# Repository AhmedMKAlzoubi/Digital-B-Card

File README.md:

# Digital Business Card (Digital-B-Card)

An ESP32-C3 based digital business card / badge with an e-paper display and NFC tap-to-share, designed as a custom PCB in a compact card/badge form factor.

## Overview

This project is a self-contained electronic business card. It combines a low-power microcontroller, an e-paper display for a persistent, battery-friendly visual, and an NFC tag for one-tap contact sharing on any NFC-enabled phone. The board is designed to fit inside a 3D-printed badge enclosure.

## Key Features

- **MCU:** ESP32-C3-MINI-1-N4 (RISC-V, Wi-Fi / BLE, native USB) for control logic and OTA wireless updates.
- **Display:** 2.66" e-paper panel (GDEM0266T71WT) driven by the SSD1680 controller — ultra-low power, always-on readability.
- **NFC:** NXP NT3H2111 NTAG I²C tag + custom 8-turn PCB antenna for tap-to-share contact info with any NFC-enabled phone.
- **Power:** MCP73871-2CC power-path LiPo charger + MAX17048 fuel gauge + AP2112K-3.3 LDO — USB-C charging with seamless battery monitoring.
- **Custom PCB:** Designed in KiCad, fabricated as a 2-layer, single-sided 100 × 60 mm board.
- **Custom Case:** 3D-modeled badge enclosure (FreeCAD) with an optional 3D nameplate.

## Repository Structure

| Folder / File | Description |
|---|---|
| `PCB-Schem/` | KiCad schematic (`.kicad_sch`) and PCB layout (`.kicad_pcb`) source files. |
| `Gerber/` | Fabrication-ready Gerber files, drill files, job file, and `gerber.7z` for direct upload to a PCB manufacturer. |
| `BOM/` | Bill of materials (`digital card-BOM.csv`). |
| `datasheets/` | Component datasheets and reference documents (see [Datasheets & Spec Sheets](#datasheets--spec-sheets) below). |
| `Case/` | FreeCAD badge case models (`Digital_Card_Case_3_BADGE.FCStd`), a backup revision, and a 3D nameplate (`case-nameplate.glb`). |
| `Digital_C-Case_Viewer.html` | Standalone browser-based 3D viewer for the case / nameplate model. |
| `DOC/` | Full project report (`Digital_Business_Card_Report.zip`) covering design decisions, testing, and build notes. |

---

## Specification Sheet

> Rev A — 2026-08-24. Values are marked **[V]** verified against a datasheet/layout/CAD, **[E]** estimated, or **[TBC]** to be confirmed on hardware.

### At a Glance

| Parameter | Value |
|---|---|
| Function | E-paper display with NFC tap-to-share and Wi-Fi / BLE connectivity |
| Modes | Desk nameplate / event badge / tap-to-share card (firmware-selected) |
| Outer dimensions | 104.6 × 69.6 × 11.1 mm **[V]** |
| Mass, assembled | ≈ 68 g **[E]** |
| Power | 1S Li-Po, USB-C rechargeable |
| Enclosure | Two-part 3D print, M2 screws |
| MCU | ESP32-C3-MINI-1-N4 (RISC-V, Wi-Fi + BLE, native USB) |
| Display | 2.66" e-paper, 152 × 296 px, SSD1680 driver (GDEM0266T71WT) |
| Connectivity | NFC (NT3H2111 + custom PCB antenna), Wi-Fi, BLE |
| Charging | USB-C, MCP73871-2CC power-path Li-Po charge management |
| Regulation | AP2112K-3.3 LDO |
| Fuel gauge | MAX17048 |
| Battery | 1S Li-Po, 500 mAh (Uxney 503035, 200–600 mAh range supported) |
| Design tool | KiCad |
| Manufacturing | JLCPCB, 2-layer, full SMT assembly |

### PCB Mechanical

| Parameter | Value |
|---|---|
| Outline | 100.0 × 60.0 mm **[V]** |
| Thickness | 1.6 mm **[V]** |
| Layers | 2 (F.Cu, B.Cu) **[V]** |
| Assembly | Single-sided — all components on B.Cu **[V]** |
| Mounting holes | 4 × Ø2.2 mm NPTH for M2, 2.75 mm from each corner **[V]** |
| Min track width | 0.25 mm signal / 0.40 mm power **[V]** |
| Min clearance | 0.20 mm (0.50 mm on HV class) **[V]** |
| Via / drill | 0.6 / 0.3 mm **[V]** |
| Surface finish | ENIG recommended |
| Placements | 59 across 27 orderable line items **[V]** |

### Enclosure

| Parameter | Value |
|---|---|
| Outer | 104.6 × 69.6 × 11.1 mm **[V]** |
| Wall / floor thickness | 2.0 mm **[V]** |
| PCB fit clearance | 0.3 mm per side **[V]** (may open to 0.4–0.5 mm **[TBC]**) |
| Split line | z = +1.6 mm — tray below, cover above **[V]** |
| Internal cavity | 100.6 × 65.6 × 5.5 mm deep **[V]** |
| Board support | 4 × Ø4.5 mm bosses with Ø1.7 mm pilot holes **[V]** |
| Fasteners | 4 × M2 self-tapping; nylon in the two holes nearest the NFC coil |
| USB-C opening | 12.6 × 6.2 mm **[V]** |
| Button access | 2 × Ø2.0 mm through tray floor **[V]** |

### Display

| Parameter | Value |
|---|---|
| Part | GDEM0266T71WT (Good Display) |
| Technology | E-paper, monochrome, bistable — zero power to hold image |
| Controller | SSD1680 (Solomon Systech) |
| Diagonal | 2.66" |
| Resolution | 152 × 296 px **[V]** |
| Active area | 30.704 × 60.088 mm **[V]** |
| Interface | 4-wire SPI, BS1 strapped low **[V]** |
| Connector | 24-pin 0.5 mm FPC, 14 mm tail **[V]** |
| Typical operating current | 4.5 mA **[V]** |
| Peak refresh current | 40 mA typ / 60 mA max **[V]** |

### Wireless

| Parameter | Value |
|---|---|
| MCU module | ESP32-C3-MINI-1-N4 (Espressif), RF pre-certified |
| Core | 32-bit RISC-V single core |
| Flash | 4 MB |
| Wi-Fi | 802.11 b/g/n, 2.4 GHz |
| Bluetooth | BLE 5 |
| Wi-Fi/BLE Antenna | Integrated module PCB antenna, overhanging board edge per Espressif guidance **[V]** |
| USB | Native USB (GPIO18/19) — programming and debug, no UART bridge |

### NFC

| Parameter | Value |
|---|---|
| Tag IC | NT3H2111W0FHKH (NXP NTAG I²C plus) |
| Standard | NFC Forum Type 2, 13.56 MHz |
| Host interface | I²C |
| Antenna | Custom PCB coil on F.Cu — 8 turns, 0.6 mm trace, 0.3 mm gap **[V]** |
| Coil area | 15 × 50 mm **[V]** |
| Coil inductance | ≈ 1.93 µH **[E]** |
| Chip capacitance | 50 pF **[V]** (datasheet §13.1) |
| Tuning capacitor | 22 pF C0G/NP0 **[V]** |
| Field-detect | FD → GPIO3, deep-sleep wake on tap **[V]** |
| Read range | **[TBC]** — C14 is the tuning point |

### Power

| Parameter | Value |
|---|---|
| Battery chemistry | Lithium polymer, 1 cell |
| Capacity | 500 mAh (200–600 mAh range supported) |
| Nominal / max voltage | 3.7 V / 4.2 V |
| Cell | Uxney 503035, 35 × 30 × 5 mm, integrated protection |
| Connector | JST-PH 2.0 mm, S2B-PH-SM4-TB horizontal SMT **[V]** |
| Regulation output | 3.3 V (AP2112K LDO, 600 mA rated) |
| LDO input source | Charger SYS/OUT rail — **not** VBAT |
| Charge IC | MCP73871-2CC, power-path topology |
| Charge voltage | 4.20 V **[V]** |
| Input current limit | 500 mA **[V]** |
| Charge current | ≈ 303 mA **[E]** |
| Termination current | ≈ 42 mA **[E]** |
| Safety timer | 6 h **[V]** |
| Worst-case dissipation | ≈ 0.4 W **[E]** |
| Fuel gauge | MAX17048, ModelGauge, 3 µA operating, I²C, ALRT → GPIO4 wake |

### Current Budget

| State | Estimate | Note |
|---|---|---|
| Deep sleep | ≈ 10–20 µA | MCU deep sleep + gauge 3 µA + leakage |
| Display holding image | 0 µA | Bistable — no power to retain |
| Display refresh | 40–60 mA for a few seconds | Panel datasheet §6.2 |
| Wi-Fi transmit | up to ≈ 350 mA peak | ESP32-C3 typical |
| NFC tap (harvested) | Field-powered | Tag responds without waking MCU |

### GPIO Pin Map

| GPIO | Net | Notes |
|---|---|---|
| 0 | I2C SDA | Shared bus — NFC + fuel gauge |
| 1 | I2C SCL | Shared bus |
| 2 | EPD RST | Strapping pin, 10 kΩ pull-up, idles high |
| 3 | NFC FD | Field detect; deep-sleep wake on tap (RTC-capable) |
| 4 | FUELGAUGE ALERT | MAX17048 ALRT; deep-sleep wake (RTC-capable) |
| 5 | EPD BUSY | Input |
| 6 | EPDCLK | E-paper SPI clock |
| 7 | EPDDATA | E-paper SPI data |
| 8 | STATUS LED | Strapping — must be high at boot, 10 kΩ pull-up |
| 9 | BOOT | Strapping, 10 kΩ pull-up + debounce cap, button to GND |
| 10 | EPD CS | E-paper chip select |
| 18 / 19 | USB D− / D+ | 0 Ω series to USB-C |
| 20 | EPD DC | Data/command |
| 21 | UART0 TX | Optional debug |
| EN | RESET | 10 kΩ pull-up + cap + RESET button |

### Manufacturing Summary

| Parameter | Value |
|---|---|
| Fabricator | JLCPCB |
| Process | 2-layer, full SMT assembly, single-sided |
| DRC | 0 violations, 12 documented exclusions **[V]** |
| ERC | Clean — one intentional informational note **[V]** |
| Gerber set | 9 files, Protel extensions, X2 attributes |
| BOM | 27 line items, 59 placements, LCSC part numbers on every row **[V]** |
| DNP | C5, C6 — USB ESD positions, deliberately unpopulated |
| Not in BOM | AE1 — antenna is etched copper |
| Enclosure | FDM, PLA, 2 parts, no supports required **[TBC]** |

---

## Bill of Materials (BOM)

The complete component list is in [`BOM/digital card-BOM.csv`](./BOM/digital%20card-BOM.csv). The table below is the authoritative human-readable BOM (27 orderable line items, 59 placements) with all LCSC part numbers.

> **Note:** C5 and C6 (USB ESD capacitor positions) are **DNP** (Do Not Populate). AE1 (NFC antenna) is etched copper — not a sourced component.

| Designator(s) | Value / Part | Package | LCSC # | Datasheet |
|---|---|---|---|---|
| U1 | ESP32-C3-MINI-1-N4 | Module | C2838502 | [esp32-c3-mini-1_datasheet_en.pdf](./datasheets/esp32-c3-mini-1_datasheet_en.pdf) |
| U2 | MAX17048G+T10 | TDFN-8 + EP | C2682616 | [C2682616.pdf](./datasheets/C2682616.pdf) |
| U3 | AP2112K-3.3 | SOT-23-5 | C51118 | [C51118.pdf](./datasheets/C51118.pdf) |
| U4 | NT3H2111W0FHKH | XQFN-8 | C710403 | [NT3H2111_2211.pdf](./datasheets/NT3H2111_2211.pdf) |
| U7 | MCP73871-2CC | QFN-20 + EP | C5121473 | [C5121473.pdf](./datasheets/C5121473.pdf) |
| J1 | USB-C TYPE-C-31-M-12 | 16P receptacle | C165948 | [C165948 (1).pdf](./datasheets/C165948%20(1).pdf) |
| J2 | JST S2B-PH-SM4-TB | PH 2.0 mm horiz. SMT | C295747 | [C295747.pdf](./datasheets/C295747.pdf) |
| J3 | AFC07-S24ECA-00 | 24P, 0.5 mm, top-contact | C262643 | [C262643 (2).pdf](./datasheets/C262643%20(2).pdf) |
| Q2 | SI1304BDL | SOT-323 | C7419947 | [C7419947 (1).pdf](./datasheets/C7419947%20(1).pdf) |
| L1 | 47 µH CDRH2D18 | SMD | C2454210 | [C2454210 (1).pdf](./datasheets/C2454210%20(1).pdf) |
| D1, D5, D6 | MBR0530 Schottky | SOD-123 | C77336 | [C77336 (1).pdf](./datasheets/C77336%20(1).pdf) |
| D2, D3, D4 | Red LED | 0603 | C2286 | [C2286.pdf](./datasheets/C2286.pdf) |
| SW1, SW2 | TS-1088-AR02016 tactile button | 4 × 3 mm SMD | C720477 | [C720477 (1).pdf](./datasheets/C720477%20(1).pdf) |
| R2, R3, R8, R9, R12, R17–R19 | 10 kΩ | 0805 | C17414 | [Uniroyal_resistors.pdf](./datasheets/Uniroyal_resistors%20(C17414%20C17521%20C22978%20C23179%20C23186%20C23352).pdf) |
| R1, R4, R5 | 0 Ω jumper | 0603 | C21189 | [Uniroyal_resistors.pdf](./datasheets/Uniroyal_resistors%20(C17414%20C17521%20C22978%20C23179%20C23186%20C23352).pdf) |
| R6, R7 | 5.1 kΩ (USB-C CC) | 0603 | C23186 | [Uniroyal_resistors.pdf](./datasheets/Uniroyal_resistors%20(C17414%20C17521%20C22978%20C23179%20C23186%20C23352).pdf) |
| R10 | 3.3 kΩ | 0603 | C22978 | [Uniroyal_resistors.pdf](./datasheets/Uniroyal_resistors%20(C17414%20C17521%20C22978%20C23179%20C23186%20C23352).pdf) |
| R11 | 24 kΩ | 0603 | C23352 | [Uniroyal_resistors.pdf](./datasheets/Uniroyal_resistors%20(C17414%20C17521%20C22978%20C23179%20C23186%20C23352).pdf) |
| R13, R14, R15 | 470 Ω | 0603 | C23179 | [Uniroyal_resistors.pdf](./datasheets/Uniroyal_resistors%20(C17414%20C17521%20C22978%20C23179%20C23186%20C23352).pdf) |
| R16 | 2.2 Ω sense resistor | 0805 | C17521 | [Uniroyal_resistors.pdf](./datasheets/Uniroyal_resistors%20(C17414%20C17521%20C22978%20C23179%20C23186%20C23352).pdf) |
| C1, C3, C8, C24 | 100 nF decoupling | 0805 | C28233 | [Samsung_MLCC_catalog.pdf](./datasheets/Samsung_MLCC_catalog%20(C1653%20C15849%20C19666%20C19702%20C21120%20C28233%20C28323).pdf) |
| C2, C11 | 10 µF bulk | 0603 | C19702 | [Samsung_MLCC_catalog.pdf](./datasheets/Samsung_MLCC_catalog%20(C1653%20C15849%20C19666%20C19702%20C21120%20C28233%20C28323).pdf) |
| C4, C9, C10, C18 | 1 µF 50 V X7R bypass | 0805 | C28323 | [Samsung_MLCC_catalog.pdf](./datasheets/Samsung_MLCC_catalog%20(C1653%20C15849%20C19666%20C19702%20C21120%20C28233%20C28323).pdf) |
| C7, C12 | 4.7 µF | 0603 | C19666 | [Samsung_MLCC_catalog.pdf](./datasheets/Samsung_MLCC_catalog%20(C1653%20C15849%20C19666%20C19702%20C21120%20C28233%20C28323).pdf) |
| C13 | 220 nF | 0603 | C21120 | [Samsung_MLCC_catalog.pdf](./datasheets/Samsung_MLCC_catalog%20(C1653%20C15849%20C19666%20C19702%20C21120%20C28233%20C28323).pdf) |
| C14 | 22 pF C0G/NP0 (NFC tuning) | 0603 | C1653 | [Samsung_MLCC_catalog.pdf](./datasheets/Samsung_MLCC_catalog%20(C1653%20C15849%20C19666%20C19702%20C21120%20C28233%20C28323).pdf) |
| C15–C17, C19–C23 | 1 µF 50 V X5R bypass | 0603 | C15849 | [Samsung_MLCC_catalog.pdf](./datasheets/Samsung_MLCC_catalog%20(C1653%20C15849%20C19666%20C19702%20C21120%20C28233%20C28323).pdf) |
| C5, C6 | **DNP** — USB ESD positions | 0603 | — | — |
| AE1 | NFC coil (etched copper, 8T) | — | — | — |

> **Total:** 27 orderable line items / 59 placements. Raw CSV: [`BOM/digital card-BOM.csv`](./BOM/digital%20card-BOM.csv)

---

## Datasheets & Spec Sheets

All component datasheets are in the [`datasheets/`](./datasheets) directory. A single combined quick-reference is also available at [`datasheets/all_datasheets_combined.md`](./datasheets/all_datasheets_combined.md).

### ICs & Active Components

| Component | LCSC # | Description | Datasheet |
|---|---|---|---|
| ESP32-C3-MINI-1-N4 | C2838502 | RISC-V SoC module, Wi-Fi + BLE, native USB | [esp32-c3-mini-1_datasheet_en.pdf](./datasheets/esp32-c3-mini-1_datasheet_en.pdf) |
| ESP32-C3 HW Guidelines | — | PCB layout and antenna design guide | [esp-hardware-design-guidelines-en-master-esp32c3.pdf](./datasheets/esp-hardware-design-guidelines-en-master-esp32c3.pdf) |
| SSD1680 | — | E-paper display controller | [SSD1680.pdf](./datasheets/SSD1680.pdf) |
| GDEM0266T71WT | — | 2.66" e-paper panel | [GDEM0266T71WT.pdf](./datasheets/GDEM0266T71WT.pdf) |
| NT3H2111W0FHKH | C710403 | NXP NTAG I²C NFC tag | [NT3H2111_2211.pdf](./datasheets/NT3H2111_2211.pdf) |
| MAX17048G+T10 | C2682616 | 1–2 cell fuel gauge (I²C, ModelGauge) | [C2682616.pdf](./datasheets/C2682616.pdf) |
| AP2112K-3.3 | C51118 | 600 mA LDO regulator | [C51118.pdf](./datasheets/C51118.pdf) |
| MCP73871-2CC | C5121473 | LiPo power-path charge management | [C5121473.pdf](./datasheets/C5121473.pdf) |
| SI1304BDL (Q2) | C7419947 | N-MOSFET, boost converter switch | [C7419947 (1).pdf](./datasheets/C7419947%20(1).pdf) |

### Passive & Discrete Components (LCSC)

| LCSC # | Component | Designator(s) | File |
|---|---|---|---|
| C165948 | USB Type-C receptacle | J1 | [C165948 (1).pdf](./datasheets/C165948%20(1).pdf) |
| C295747 | JST S2B-PH-SM4-TB battery connector | J2 | [C295747.pdf](./datasheets/C295747.pdf) |
| C262643 | AFC07-S24ECA-00 FPC connector | J3 | [C262643 (2).pdf](./datasheets/C262643%20(2).pdf) |
| C2454210 | 47 µH CDRH2D18 inductor | L1 | [C2454210 (1).pdf](./datasheets/C2454210%20(1).pdf) |
| C77336 | MBR0530 Schottky diode | D1, D5, D6 | [C77336 (1).pdf](./datasheets/C77336%20(1).pdf) |
| C2286 | Red LED 0603 | D2, D3, D4 | [C2286.pdf](./datasheets/C2286.pdf) |
| C720477 | TS-1088-AR02016 tactile button | SW1, SW2 | [C720477 (1).pdf](./datasheets/C720477%20(1).pdf) |

### Catalog References

| Catalog | Covers (LCSC #s) | File |
|---|---|---|
| Samsung MLCC | C1653, C15849, C19666, C19702, C21120, C28233, C28323 | [Samsung_MLCC_catalog.pdf](./datasheets/Samsung_MLCC_catalog%20(C1653%20C15849%20C19666%20C19702%20C21120%20C28233%20C28323).pdf) |
| Uniroyal Resistors | C17414, C17521, C22978, C23179, C23186, C23352 | [Uniroyal_resistors.pdf](./datasheets/Uniroyal_resistors%20(C17414%20C17521%20C22978%20C23179%20C23186%20C23352).pdf) |

---

## Documentation

The full project report — covering design rationale, schematic/PCB walkthrough, assembly notes, and testing — is available in [`DOC/Digital_Business_Card_Report.zip`](./DOC/Digital_Business_Card_Report.zip).

---

## Manufacturing

To fabricate the PCB, upload [`Gerber/gerber.7z`](./Gerber/gerber.7z) (or the individual Gerber/drill files) to JLCPCB or your PCB manufacturer of choice with full SMT assembly. Reference the [BOM table](#bill-of-materials-bom) above or the CSV for component sourcing.

**Pre-order checklist:**
- Verify polarized-part orientations (Q2, U7, U2, U4, diodes, LEDs) in the JLCPCB assembly preview.
- Confirm BOM excludes DNP rows (C5/C6) and the etched antenna (AE1).
- Use nylon (not steel) M2 screws in the two mounting holes nearest the NFC coil.
- On battery arrival: verify lead polarity at J2 with a multimeter before first connection — JST-PH polarity is not standardized.

---

## Case & Enclosure

The badge enclosure is modeled in FreeCAD (`Case/Digital_Card_Case_3_BADGE.FCStd`). A 3D nameplate model (`case-nameplate.glb`) can be previewed directly in a browser using [`Digital_C-Case_Viewer.html`](./Digital_C-Case_Viewer.html).

---

## License

N/A

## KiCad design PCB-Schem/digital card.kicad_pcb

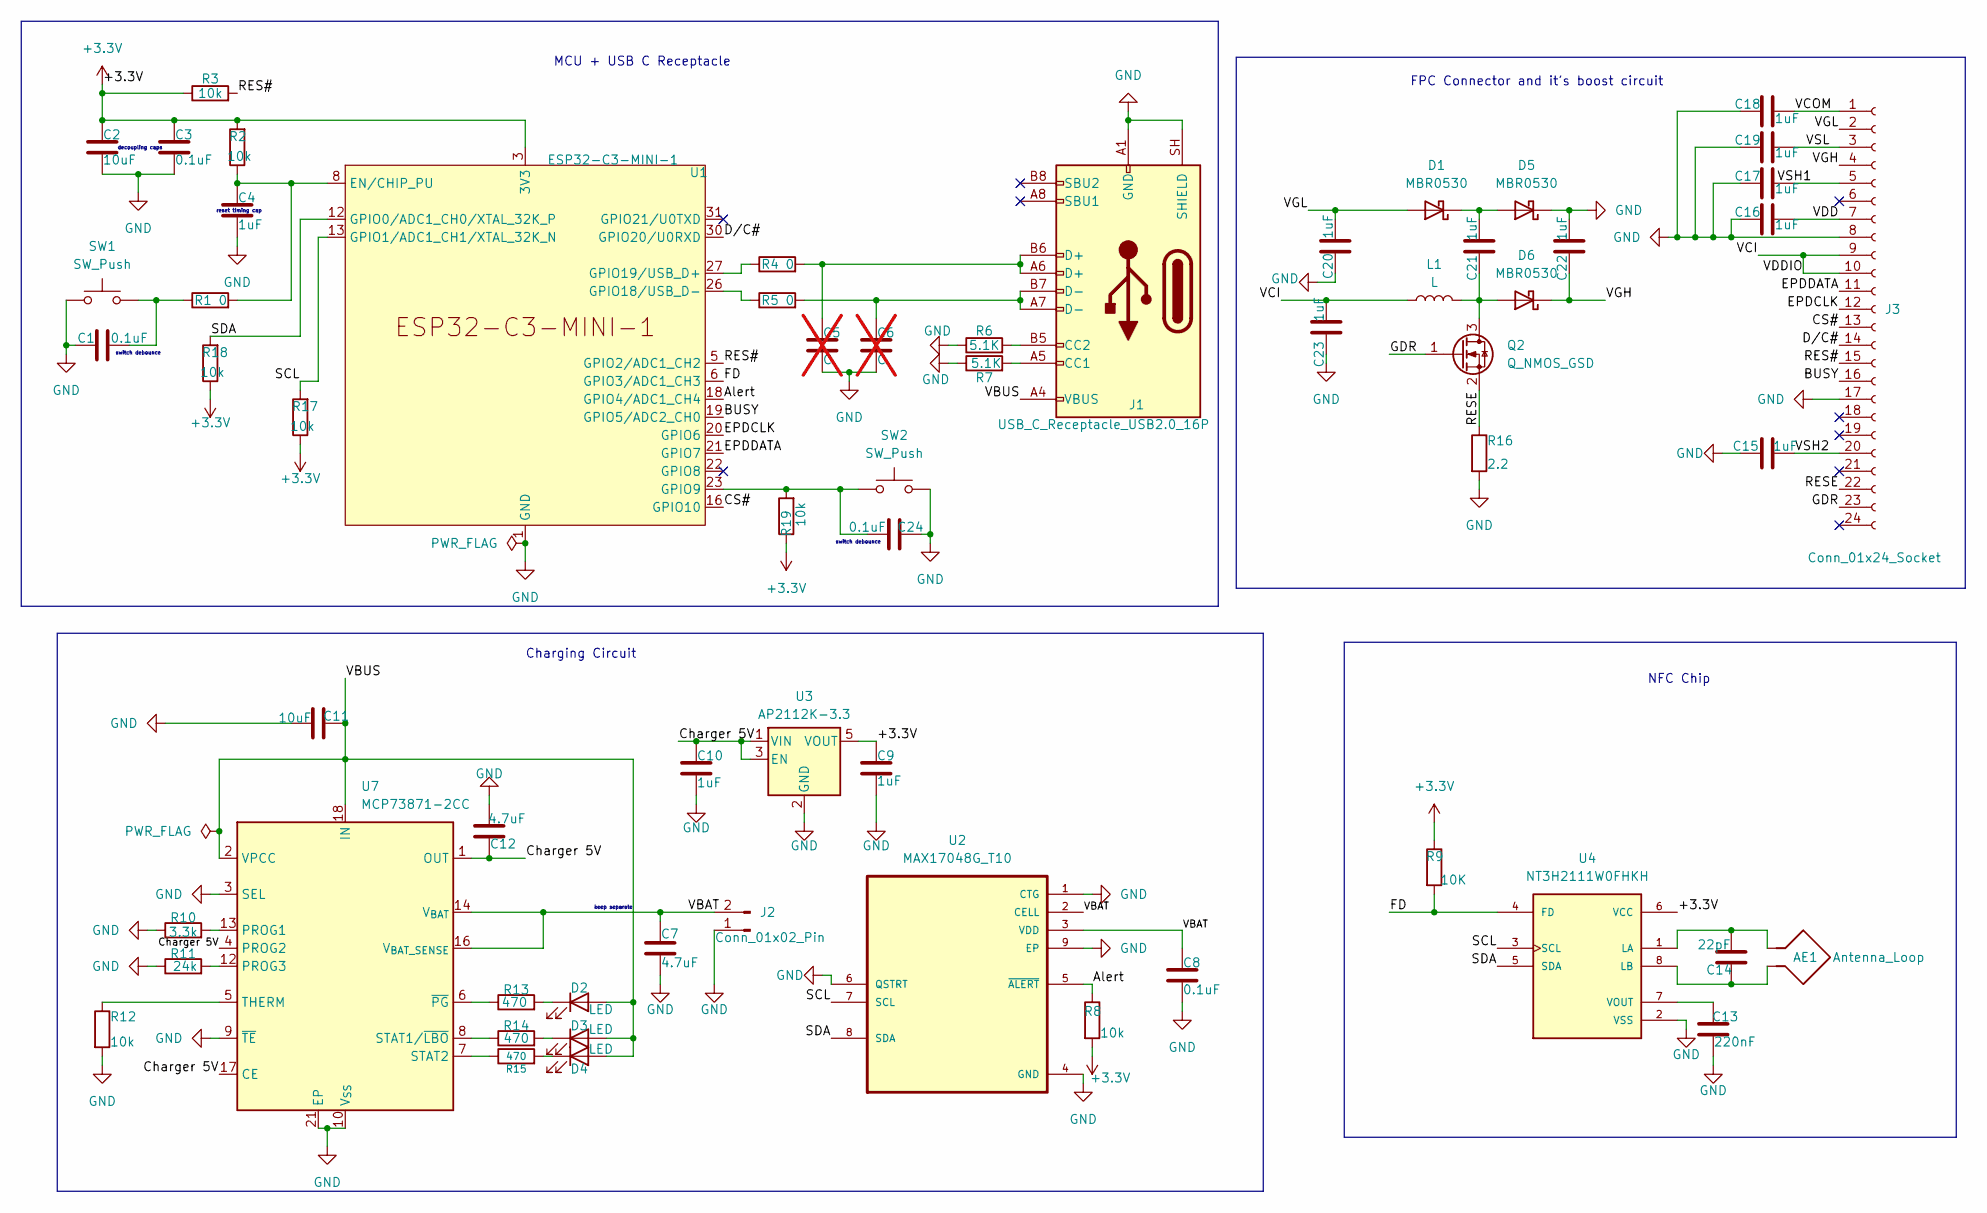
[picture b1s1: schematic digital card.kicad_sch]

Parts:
AE1: Antenna_Loop; NFC_Antenna_50x15_8T
C1, C3, C8, C24: 0.1uF; C_0805_2012Metric; LCSC C28233
C2, C11: 10uF; C_0603_1608Metric; LCSC C19702
C4, C9, C10, C18: 1uF; C_0805_2012Metric; LCSC C28323
C5, C6: C; C_0603_1608Metric; not fitted
C7, C12: 4.7uF; C_0603_1608Metric; LCSC C19666
C13: 220nF; C_0603_1608Metric; LCSC C21120
C14: 22pF; C_0603_1608Metric; LCSC C1653
C15, C16, C17, C19, C20, C21, C22, C23: 1uF; C_0603_1608Metric; LCSC C15849
D1, D5, D6: MBR0530; D_SOD-123; LCSC C77336
D2, D3, D4: LED; LED_0603_1608Metric; LCSC C2286
J1: USB_C_Receptacle_USB2.0_16P; USB_C_Receptacle_HRO_TYPE-C-31-M-12; LCSC C165948
J2: Conn_01x02_Pin; JST_PH_S2B-PH-SM4-TB_1x02-1MP_P2.00mm_Horizontal; LCSC C295747
J3: Conn_01x24_Socket; FPC-SMD_AFC07-S24ECA-00; LCSC C262643
L1: L; IND-SMD_L3.0-W3.0_CDRH2D18-HPNP; LCSC C2454210
Q2: Q_NMOS_GSD; SOT-323-3_L2.0-W1.3-P1.30-LS2.1-BL; LCSC C7419947
R1, R4, R5: 0; R_0603_1608Metric; LCSC C21189
R2, R3, R8, R12, R17, R18, R19: 10k; R_0805_2012Metric; LCSC C17414
R6, R7: 5.1K; R_0603_1608Metric; LCSC C23186
R9: 10K; R_0805_2012Metric; LCSC C17414
R10: 3.3k; R_0603_1608Metric; LCSC C22978
R11: 24k; R_0603_1608Metric; LCSC C23352
R13, R14, R15: 470; R_0603_1608Metric; LCSC C23179
R16: 2.2; R_0805_2012Metric; LCSC C17521
SW1, SW2: SW_Push; SW-SMD_L3.9-W3.0-P4.45; LCSC C720477
U1: ESP32-C3-MINI-1; LCSC C2838502
U2: MAX17048G_T10; SON50P200X200X80-9N; LCSC C2682616
U3: AP2112K-3.3; SOT-23-5; LCSC C51118
U4: NT3H2111W0FHKH; QFN8P50_160X160X50L40X20N; DigiKey_Part_Number 568-12900-1-ND
U7: MCP73871-2CC; QFN-20-1EP_4x4mm_P0.5mm_EP2.5x2.5mm; LCSC C5121473

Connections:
+3.3V: C2.1, C3.1, C9.1, R2.2, R3.1, R8.2, R9.1, R17.1, R18.1, R19.1, U1.3 (3V3), U3.5 (VOUT), U4.6 (VCC)
/Alert: R8.1, U1.18 (GPIO4/ADC1_CH4), U2.5 (~ALERT)
/BUSY: J3.16, U1.19 (GPIO5/ADC2_CH0)
/CS#: J3.13, U1.16 (GPIO10)
/Charger 5V: C10.1, C12.2, U3.1 (VIN), U3.3 (EN), U7.1 (OUT), U7.4 (PROG2), U7.17 (CE), U7.20 (OUT)
/D/C#: J3.14, U1.30 (GPIO20/U0RXD)
/EPDCLK: J3.12, U1.20 (GPIO6)
/EPDDATA: J3.11, U1.21 (GPIO7)
/FD: R9.2, U1.6 (GPIO3/ADC1_CH3), U4.4 (FD)
/GDR: J3.23, Q2.1 (G)
/RES#: J3.15, R3.2, U1.5 (GPIO2/ADC1_CH2)
/RESE: J3.22, Q2.2 (S), R16.1
/SCL: R17.2, U1.13 (GPIO1/ADC1_CH1/XTAL_32K_N), U2.7 (SCL), U4.3 (SCL)
/SDA: R18.2, U1.12 (GPIO0/ADC1_CH0/XTAL_32K_P), U2.8 (SDA), U4.5 (SDA)
/VBAT: C7.1, C8.1, J2.2, U2.2 (CELL), U2.3 (VDD), U7.14 (V_{BAT}), U7.15 (V_{BAT}), U7.16 (V_{BAT_SENSE})
/VBUS: C11.1, D2.2 (A), D3.2 (A), D4.2 (A), J1.A4 (VBUS), J1.A9 (VBUS), J1.B4 (VBUS), J1.B9 (VBUS), U7.2 (VPCC), U7.18 (IN), U7.19 (IN)
/VCI: C23.2, J3.9, J3.10, L1.1
/VCOM: C18.2, J3.1
/VDD: C16.2, J3.7
/VGH: C22.1, D6.1 (K), J3.4
/VGL: C20.2, D1.2 (A), J3.2
/VSH1: C17.2, J3.5
/VSH2: C15.2, J3.20
/VSL: C19.2, J3.3
GND: C1.1, C2.2, C3.2, C4.2, C5.2, C6.2, C7.2, C8.2, C9.2, C10.2, C11.2, C12.1, C13.2, C15.1, C16.1, C17.1, C18.1, C19.1, C20.1, C22.2, C23.1, C24.1, D5.1 (K), J1.A1 (GND), J1.A12 (GND), J1.B1 (GND), J1.B12 (GND), J1.SH (SHIELD), J2.1, J3.8, J3.17, R6.1, R7.1, R10.1, R11.1, R12.2, R16.2, SW1.1, SW2.1, U1.1 (GND), U1.2 (GND), U1.11 (GND), U1.14 (GND), U1.36 (GND), U1.37 (GND), U1.38 (GND), U1.39 (GND), U1.40 (GND), U1.41 (GND), U1.42 (GND), U1.43 (GND), U1.44 (GND), U1.45 (GND), U1.46 (GND), U1.47 (GND), U1.48 (GND), U1.49 (GND), U1.50 (GND), U1.51 (GND), U1.52 (GND), U1.53 (GND), U2.1 (CTG), U2.4 (GND), U2.6 (QSTRT), U2.9 (EP), U3.2 (GND), U4.2 (VSS), U7.3 (SEL), U7.9 (~TE), U7.10 (V_{SS}), U7.11 (V_{SS}), U7.21 (EP)
unnamed: C1.2, R1.1, SW1.2
unnamed: C5.1, J1.A6 (D+), J1.B6 (D+), R4.2
unnamed: C6.1, J1.A7 (D-), J1.B7 (D-), R5.2
unnamed: C21.2, D1.1 (K), D5.2 (A)
unnamed: D2.1 (K), R13.2
unnamed: D3.1 (K), R14.2
unnamed: D4.1 (K), R15.2
unnamed: C21.1, D6.2 (A), L1.2, Q2.3 (D)
unnamed: J1.A5 (CC1), R7.2
unnamed: J1.B5 (CC2), R6.2
unnamed: C4.1, R1.2, R2.1, U1.8 (EN/CHIP_PU)
unnamed: C24.2, R19.2, SW2.2, U1.23 (GPIO9)
unnamed: R5.1, U1.26 (GPIO18/USB_D-)
unnamed: R4.1, U1.27 (GPIO19/USB_D+)
unnamed: AE1.1, C14.2, U4.1 (LA)
unnamed: AE1.2, C14.1, U4.8 (LB)
unnamed: C13.1, U4.7 (VOUT)
unnamed: R10.2, U7.13 (PROG1)
unnamed: R11.2, U7.12 (PROG3)
unnamed: R14.1, U7.8 (STAT1/~LBO)
unnamed: R15.1, U7.7 (STAT2)
unnamed: R12.1, U7.5 (THERM)
unnamed: R13.1, U7.6 (~PG)

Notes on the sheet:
decoupling caps
MCU + USB C Receptacle
reset timing cap
switch debounce
Charging Circuit
FPC Connector and it's boost circuit
NFC Chip
keep separate

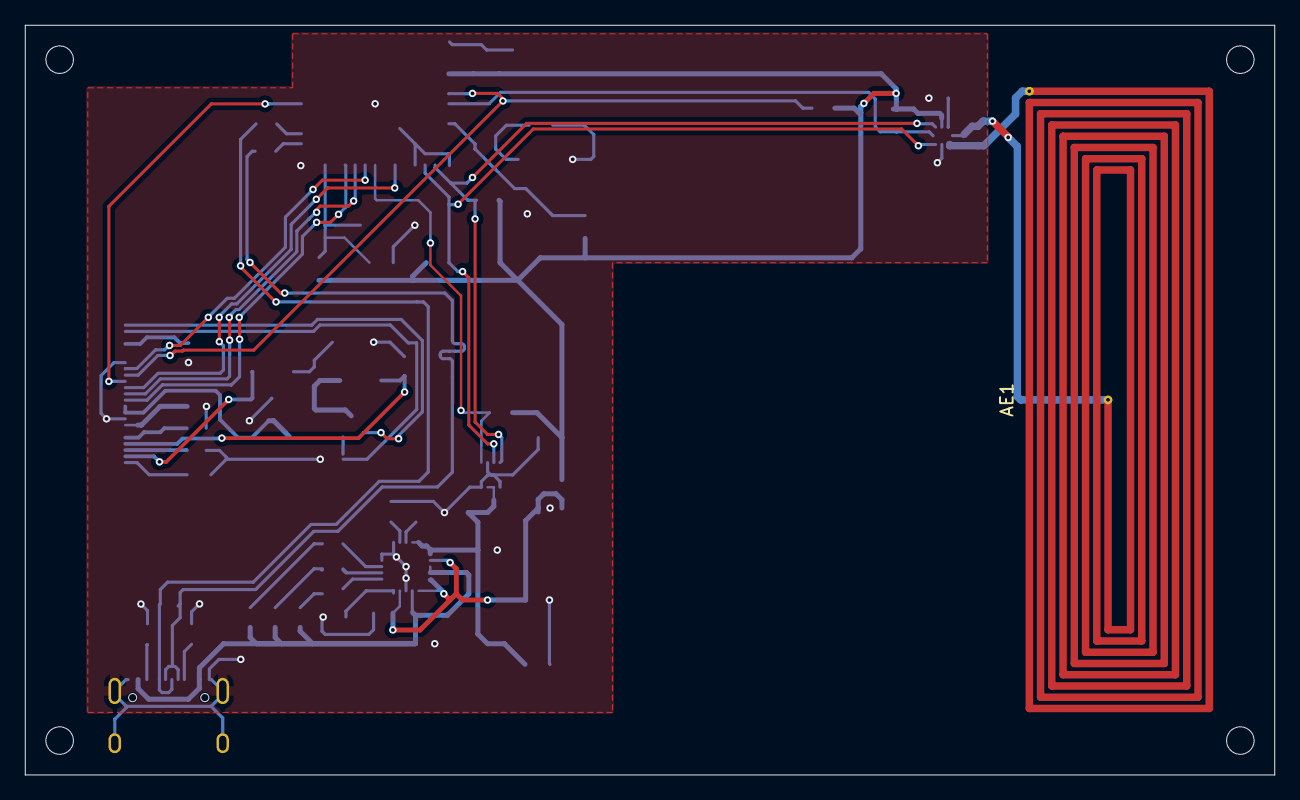
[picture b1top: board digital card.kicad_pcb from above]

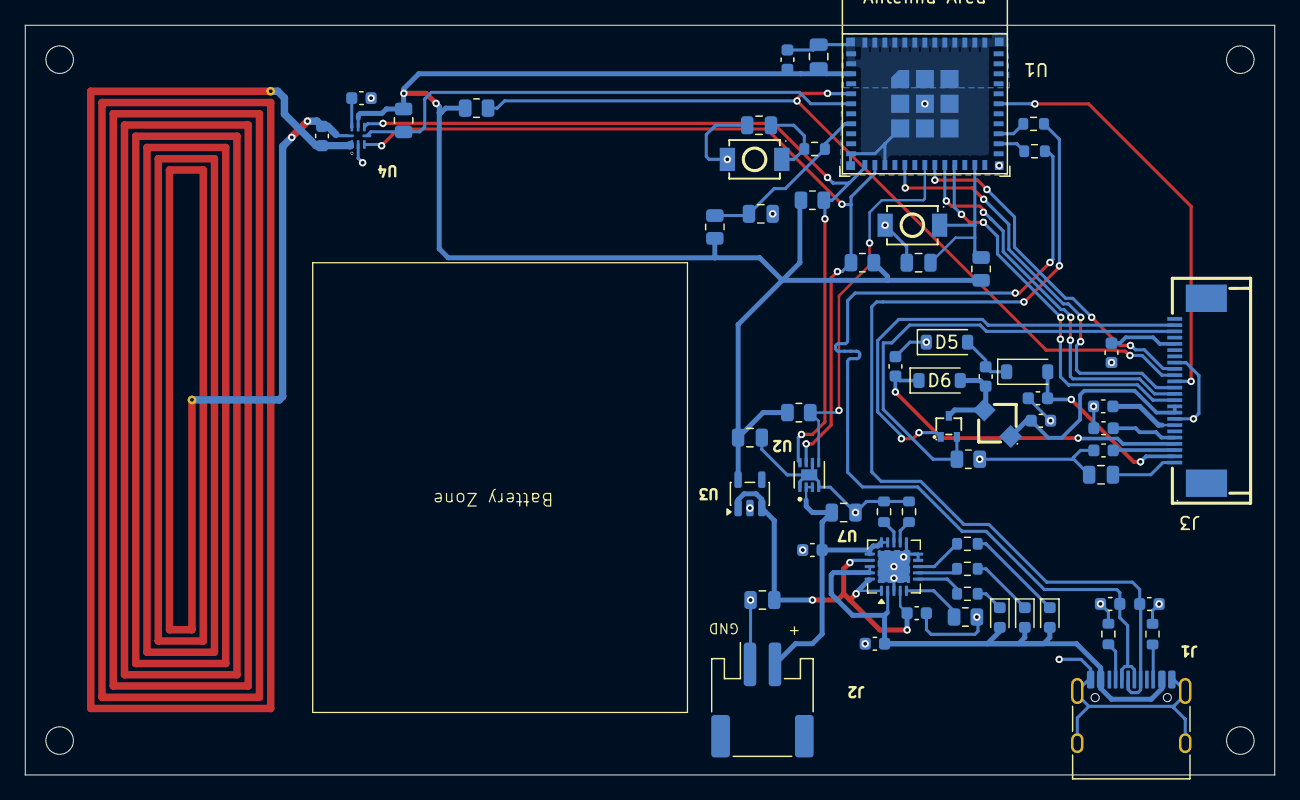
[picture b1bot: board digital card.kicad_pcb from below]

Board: 2 copper layers, 100.0 x 60.0 mm, 62 parts (61 on the bottom side), 48 nets.

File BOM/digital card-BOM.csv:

"Id";"Designator";"Footprint";"Quantity";"Designation";"Supplier and ref";
1;"AE1";"NFC_Antenna_50x15_8T";1;"Antenna_Loop";;;
2;"C1, C3, C8, C24";"C_0805_2012Metric";4;"0.1uF";;;
3;"C2, C11";"C_0603_1608Metric";2;"10uF";;;
4;"C4, C9, C10, C18";"C_0805_2012Metric";4;"1uF";;;
5;"C5, C6";"C_0603_1608Metric";2;"C";;;
6;"C7, C12";"C_0603_1608Metric";2;"4.7uF";;;
7;"C13";"C_0603_1608Metric";1;"220nF";;;
8;"C14";"C_0603_1608Metric";1;"21pF";;;
9;"C15, C16, C17, C19, C20, C21, C22, C23";"C_0603_1608Metric";8;"1uF";;;
10;"D1, D5, D6";"D_SOD-123";3;"MBR0530";;;
11;"D2, D3, D4";"LED_0603_1608Metric";3;"LED";;;
12;"J1";"USB_C_Receptacle_HRO_TYPE-C-31-M-12";1;"USB_C_Receptacle_USB2.0_16P";;;
13;"J2";"JST_PH_S2B-PH-SM4-TB_1x02-1MP_P2.00mm_Horizontal";1;"Conn_01x02_Pin";;;
14;"J3";"FPC-SMD_AFC07-S24ECA-00";1;"Conn_01x24_Socket";;;
15;"L1";"IND-SMD_L3.0-W3.0_CDRH2D18-HPNP";1;"L";;;
16;"Q2";"SOT-323-3_L2.0-W1.3-P1.30-LS2.1-BL";1;"Q_NMOS_GSD";;;
17;"R1, R4, R5";"R_0603_1608Metric";3;"0";;;
18;"R2, R3, R8, R12, R17, R18, R19";"R_0805_2012Metric";7;"10k";;;
19;"R6, R7";"R_0603_1608Metric";2;"5.1K";;;
20;"R9";"R_0805_2012Metric";1;"10K";;;
21;"R10";"R_0603_1608Metric";1;"3.3k";;;
22;"R11";"R_0603_1608Metric";1;"24k";;;
23;"R13, R14, R15";"R_0603_1608Metric";3;"470";;;
24;"R16";"R_0805_2012Metric";1;"2.2";;;
25;"SW1, SW2";"SW-SMD_L3.9-W3.0-P4.45";2;"SW_Push";;;
26;"U1";"ESP32-C3-MINI-1";1;"ESP32-C3-MINI-1";;;
27;"U2";"SON50P200X200X80-9N";1;"MAX17048G_T10";;;
28;"U3";"SOT-23-5";1;"AP2112K-3.3";;;
29;"U4";"QFN8P50_160X160X50L40X20N";1;"NT3H2111W0FHKH";;;
30;"U7";"QFN-20-1EP_4x4mm_P0.5mm_EP2.5x2.5mm";1;"MCP73871-2CC";;;
